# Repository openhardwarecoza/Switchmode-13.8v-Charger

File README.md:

# Switchmode-13.8v-Charger
Constant current 13.8v Switchmode Charger (solar)

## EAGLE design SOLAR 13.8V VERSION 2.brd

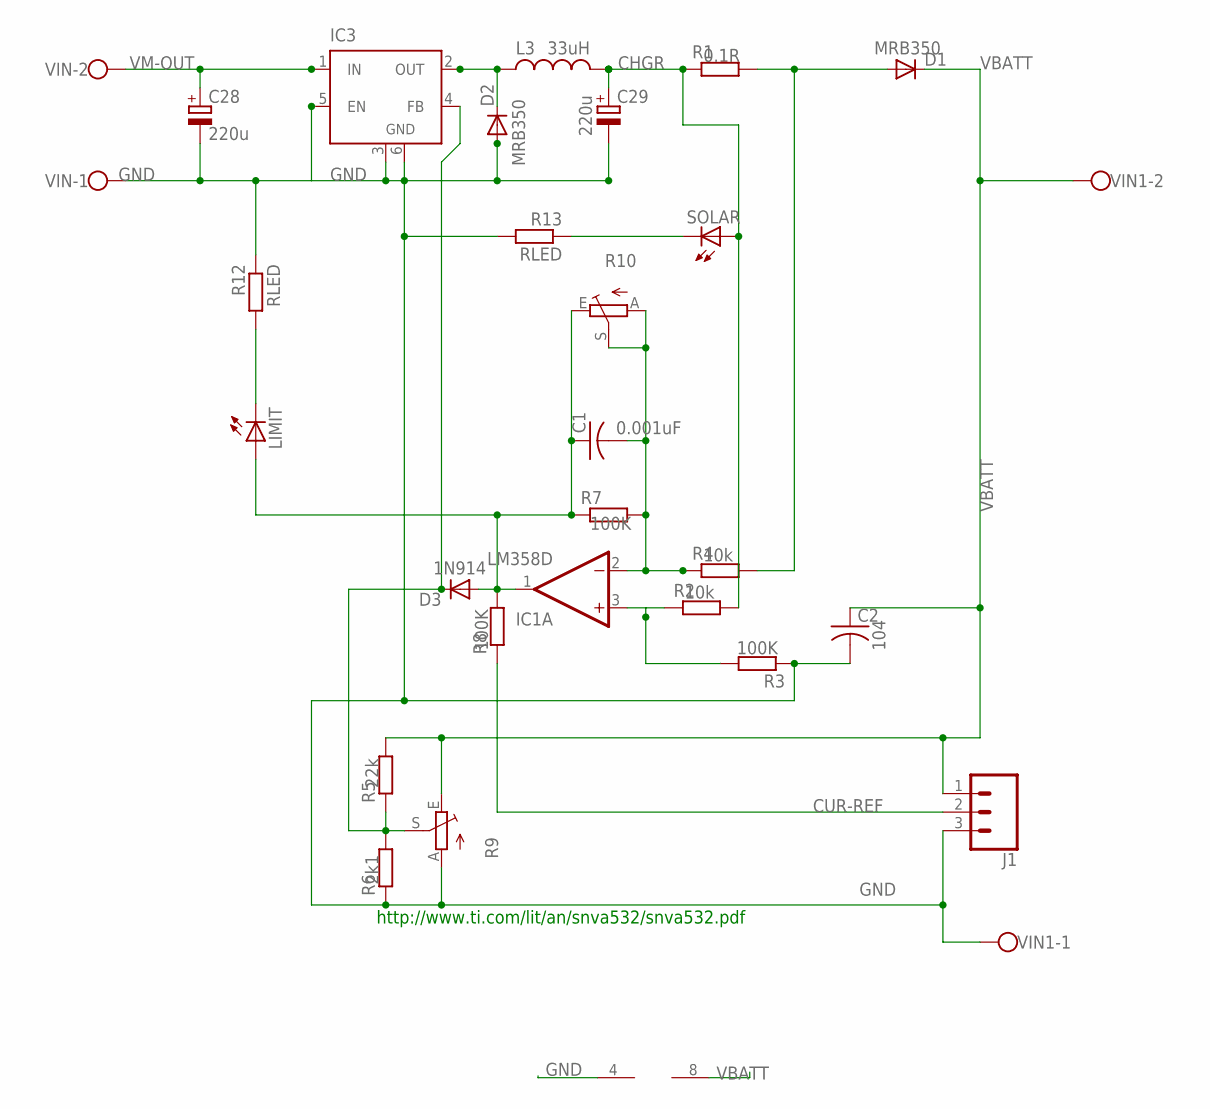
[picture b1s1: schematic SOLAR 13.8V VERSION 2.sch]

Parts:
C1: 0.001uF; C1206
C2: 104; C1206
C28, C29: 220u; E3,5-10
D1, D2: MRB350; DO-214AC
D3: 1N914; DO-214AC
IC1: LM358D; SO08
IC3: LM2596S; TO263-5
J1: CONN_03; 1X03
L3: 33uH; CDRH125
LIMIT: LED3MM
R1: 0.1R; R2512
R2, R4: 10k; R1206
R3, R7, R8: 100K; R1206
R5: 22k; R1206
R6: 2k1; R1206
R9, R10: TRIM_EU-B25P; B25P
R12, R13: RLED; R1206
SOLAR: LED3MM
VIN, VIN1: W237-102

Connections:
CHGR: C29.+, L3.2, R1.1, R2.2, SOLAR.A
CUR-REF: J1.2, R8.1
GND: C2.2, C28.-, C29.-, D2.2 (A), IC1.4 (V-), IC3.3 (GND), IC3.5 (EN), IC3.6 (GND), J1.3, R3.1, R6.1, R9.A, R12.1, R13.2, VIN.1, VIN1.1
unnamed: D1.2 (A), R1.2, R4.2
unnamed: IC1.3 (+IN), R2.1, R3.2
unnamed: R13.1, SOLAR.K (C)
unnamed: D3.1 (C), IC3.4 (FB), R5.1, R6.2, R9.S
unnamed: C1.1, D3.2 (A), IC1.1 (OUT), LIMIT.A, R7.1, R8.2, R10.E
unnamed: LIMIT.K (C), R12.2
unnamed: C1.2, IC1.2 (-IN), R4.1, R7.2, R10.A, R10.S
unnamed: D2.1 (C), IC3.2 (OUT), L3.1
VBATT: C2.1, D1.1 (C), IC1.8 (V+), J1.1, R5.2, R9.E, VIN1.2
VM-OUT: C28.+, IC3.1 (IN), VIN.2

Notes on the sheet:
http://www.ti.com/lit/an/snva532/snva532.pdf

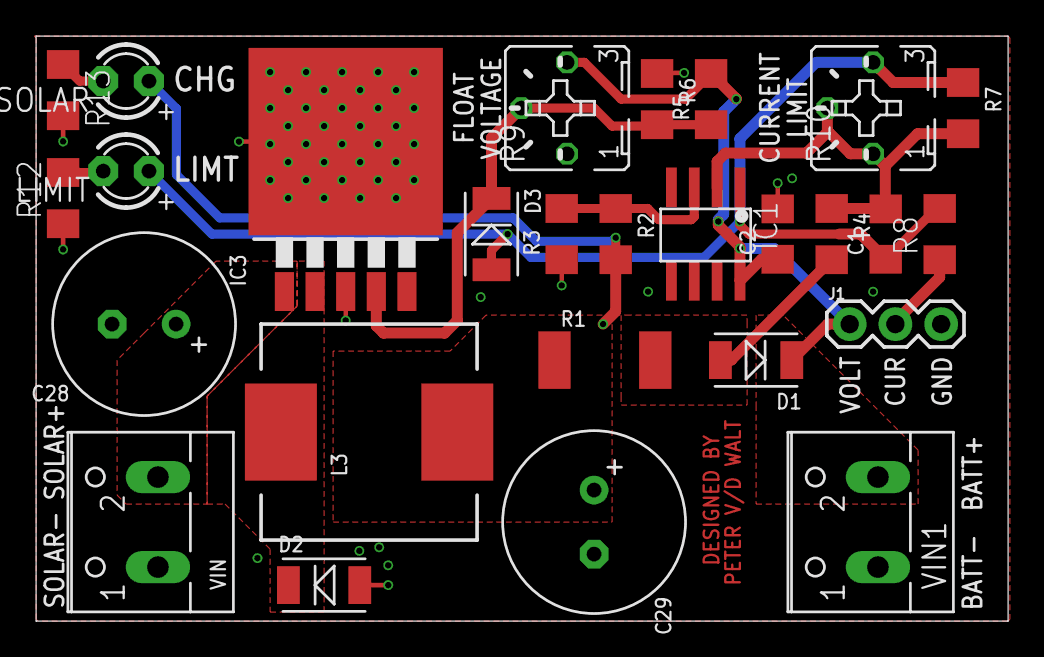
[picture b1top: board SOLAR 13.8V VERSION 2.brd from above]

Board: 2 copper layers, 54.0 x 32.5 mm, 27 parts (0 on the bottom side), 13 nets.

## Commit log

2018-10-23 as ordered

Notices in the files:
parts and their libraries:
SparkFun-Passives: Licensing: CC v3.0 Share-Alike You are welcome to use this library for commercial purposes.
SparkFun-Connectors: Licensing: Creative Commons ShareAlike 4.0 International - https://creativecommons.org/licenses/by-sa/4.0
